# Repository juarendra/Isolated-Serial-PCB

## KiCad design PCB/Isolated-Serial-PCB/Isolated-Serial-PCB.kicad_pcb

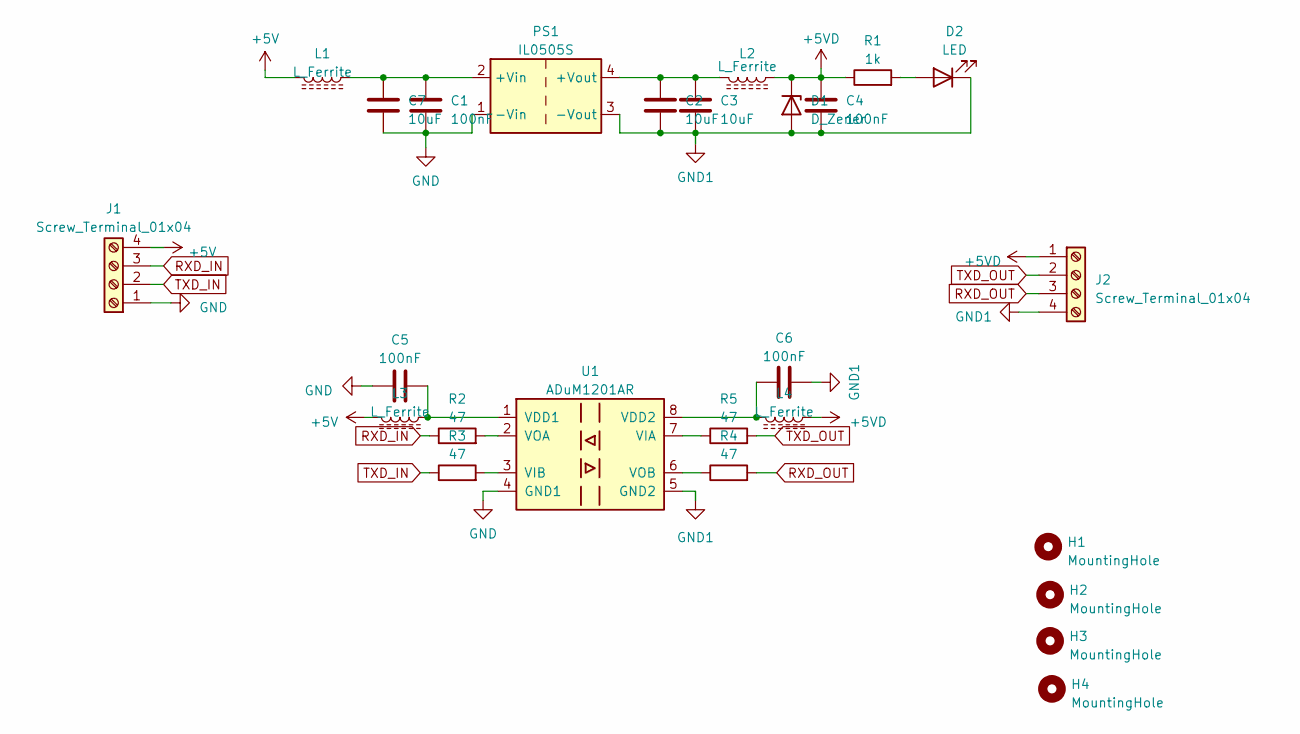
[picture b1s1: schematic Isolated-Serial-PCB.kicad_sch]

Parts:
C1, C4, C5, C6: 100nF; C_0603_1608Metric
C2, C3: 10uF; C_0603_1608Metric
C7: 10uF; C_0805_2012Metric
D1: D_Zener; D_DO-35_SOD27_P10.16mm_Horizontal
D2: LED; LED_0805_2012Metric
H1, H2, H3, H4: MountingHole; MountingHole_3.2mm_M3_Pad_Via
J1, J2: Screw_Terminal_01x04; TerminalBlock_Phoenix_MKDS-1,5-4_1x04_P5.00mm_Horizontal
L1, L2, L3, L4: L_Ferrite; L_0603_1608Metric
PS1: IL0505S; Mouser Part Number 209-IL0505S
R1: 1k; R_0603_1608Metric
R2, R3, R4, R5: 47; R_0603_1608Metric
U1: ADuM1201AR; SOIC-8_3.9x4.9mm_P1.27mm

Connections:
+5V: J1.4, L1.2, L3.2
+5VD: C4.1, D1.1 (K), J2.1, L2.1, L4.1, R1.1
GND: C1.2, C5.1, C7.2, J1.1, PS1.1 (-Vin), U1.4 (GND1)
GND1: C2.2, C3.2, C4.2, C6.2, D1.2 (A), D2.1 (K), J2.4, PS1.3 (-Vout), U1.5 (GND2)
unnamed: D2.2 (A), R1.2
unnamed: C1.1, C7.1, L1.1, PS1.2 (+Vin)
unnamed: C2.1, C3.1, L2.2, PS1.4 (+Vout)
unnamed: C5.2, L3.1, U1.1 (VDD1)
unnamed: C6.1, L4.2, U1.8 (VDD2)
unnamed: R5.1, U1.7 (VIA)
unnamed: R3.2, U1.3 (VIB)
unnamed: R2.2, U1.2 (VOA)
unnamed: R4.1, U1.6 (VOB)
RXD_IN: J1.3, R2.1
RXD_OUT: J2.3, R4.2
TXD_IN: J1.2, R3.1
TXD_OUT: J2.2, R5.2

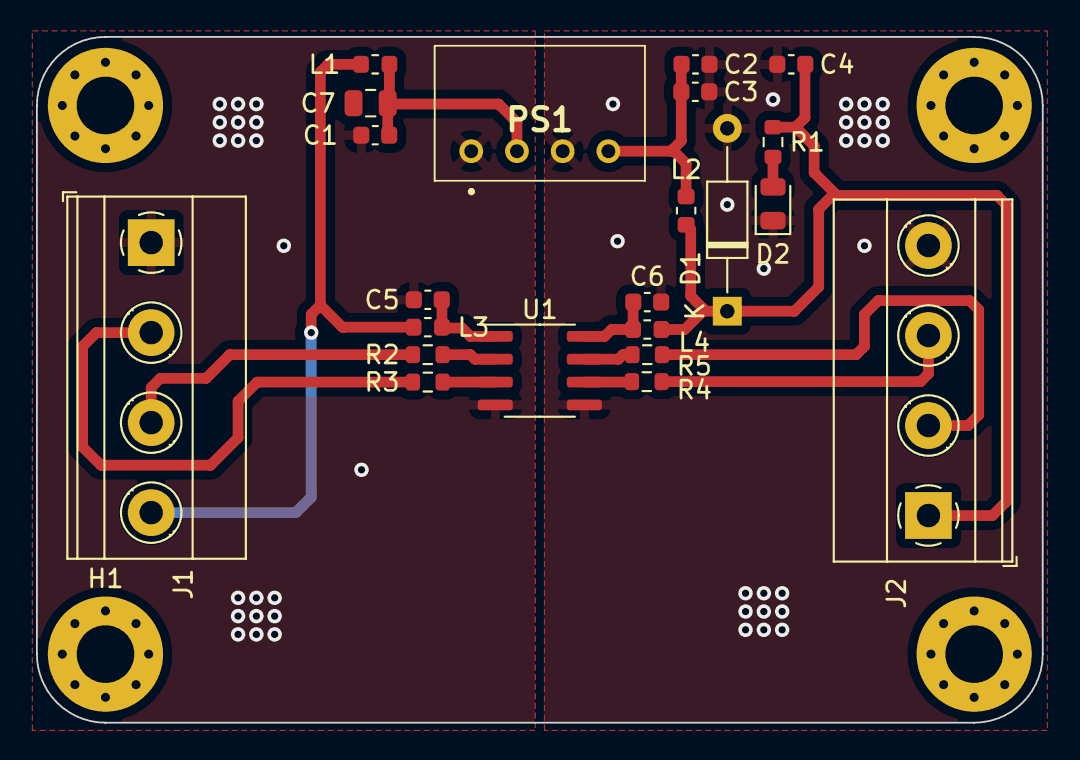
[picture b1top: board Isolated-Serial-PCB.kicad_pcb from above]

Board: 2 copper layers, 55.9 x 38.1 mm, 26 parts (0 on the bottom side), 17 nets.

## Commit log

2025-07-31 FEAT: update pcb
2025-08-08 FEAT: update folder and some documentation
